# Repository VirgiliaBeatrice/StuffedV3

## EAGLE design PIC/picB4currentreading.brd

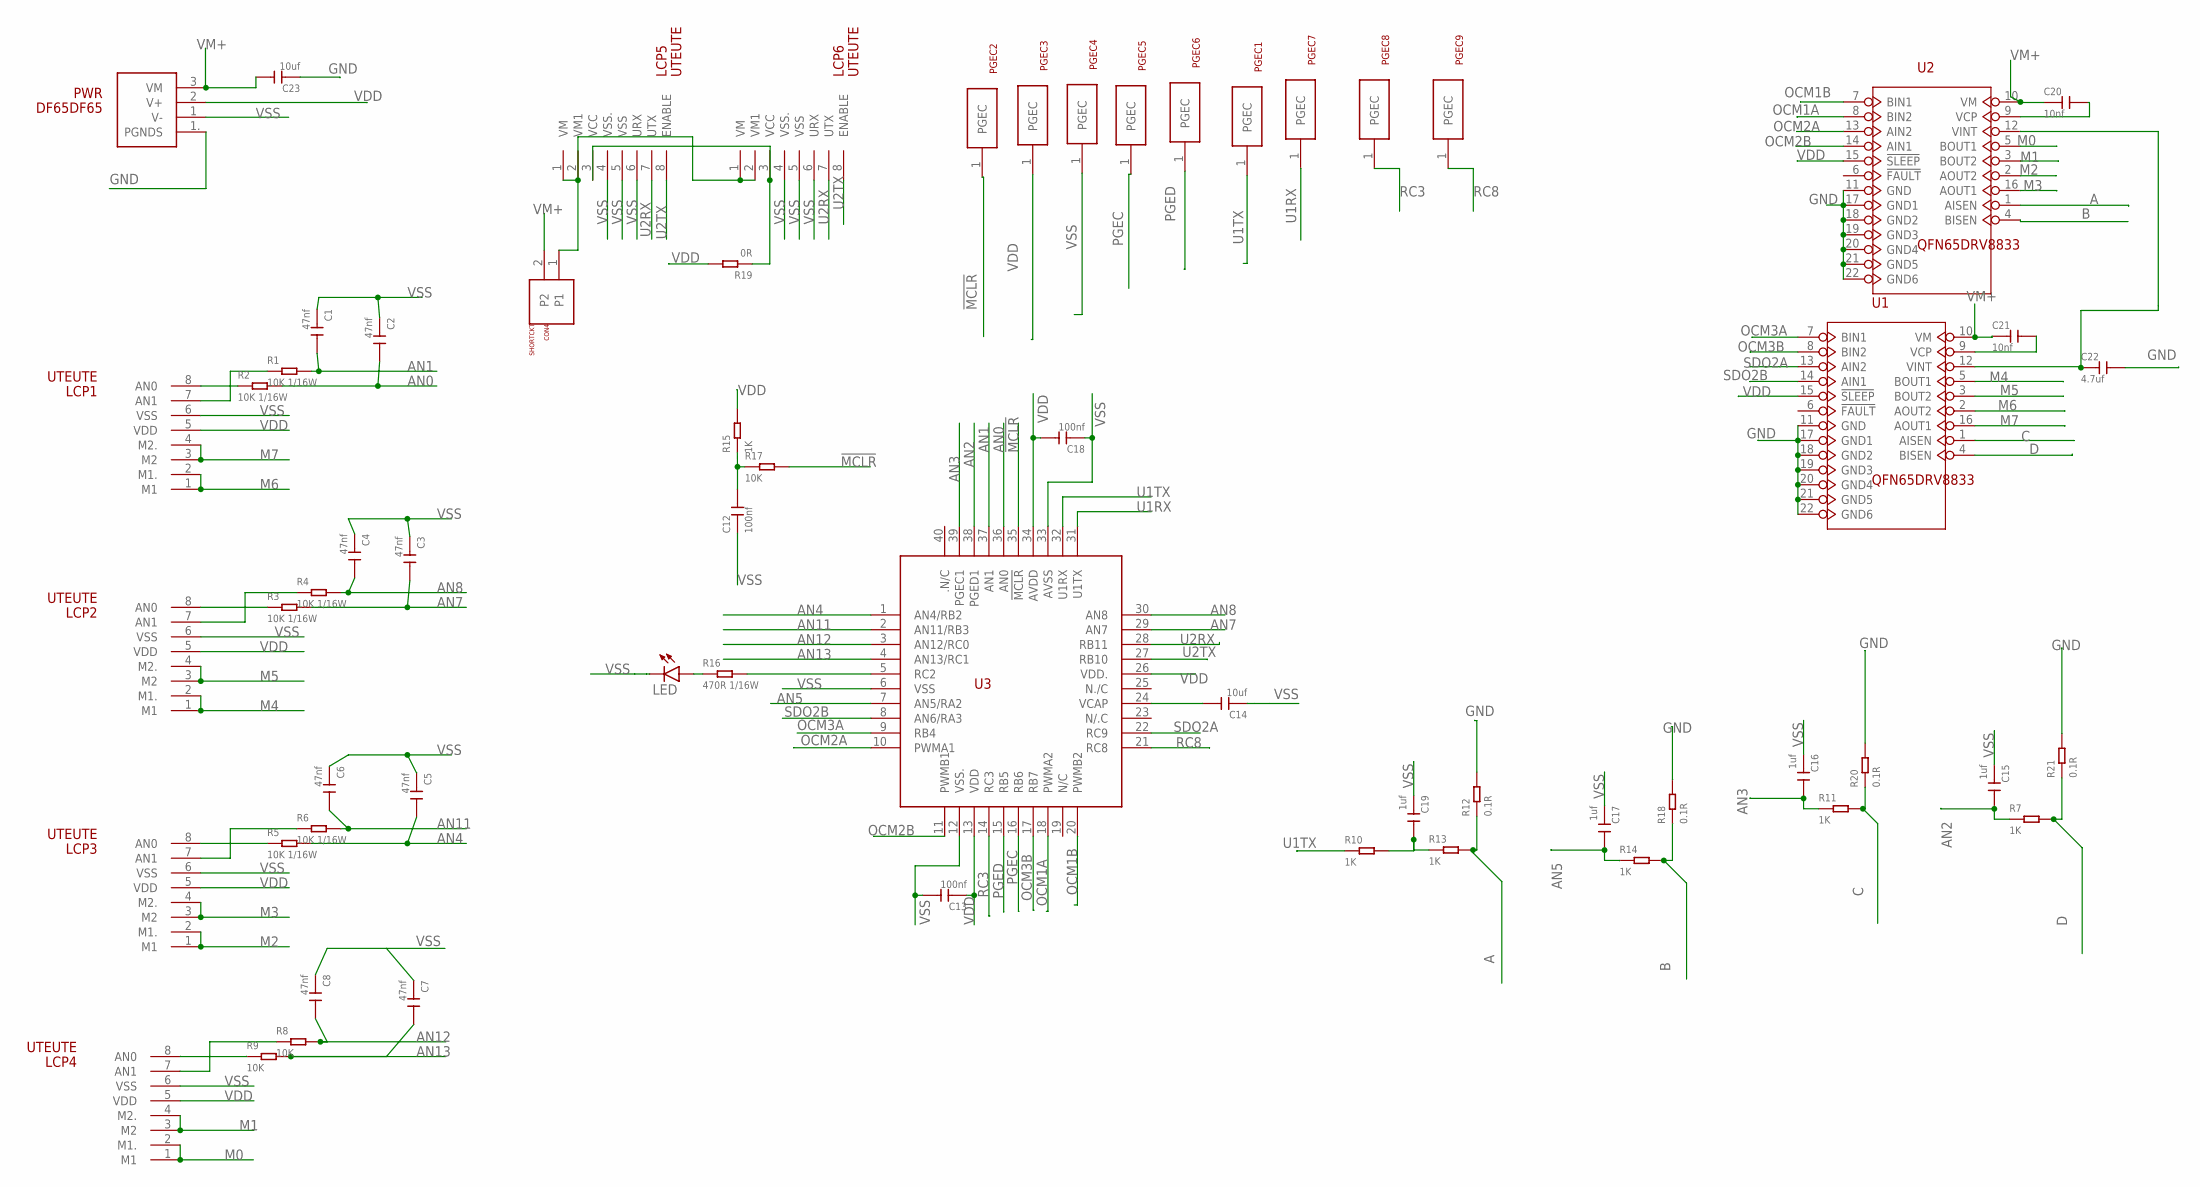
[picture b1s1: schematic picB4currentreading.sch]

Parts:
C1, C2, C3, C4, C5, C6, C7, C8: 47nf; C0402
C12, C13, C18: 100nf; C0402
C14, C23: 10uf; C0402
C15, C16, C17, C19: 1uf; C0402
C20, C21: 10nf; C0402
C22: 4.7uf; C0402
CON4: SHORTCKT; SHORT
LCP1, LCP2, LCP3, LCP4, LCP5, LCP6: UTEUTE; UTE
LED: LEDCHIP-LED0603; CHIP-LED0603
PGEC1, PGEC2, PGEC3, PGEC4, PGEC5, PGEC6, PGEC7, PGEC8, PGEC9: PGECPGEC; PGEC
PWR: DF65DF65; DF65
R1, R2, R3, R4, R5, R6: 10K 1/16W; R0402
R7, R10, R11, R13, R14, R15: 1K; R0402
R8, R9, R17: 10K; R0402
R12, R18, R20, R21: 0.1R; R0805
R16: 470R 1/16W; R0402
R19: 0R; R0402
U1, U2: QFN65DRV8833; QFN65P400X400X80-17N
U3: PIC32MM0064GPL036PIC32MM0064GPL36; UQFN40MV5X5MM

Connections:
!MCLR!: PGEC2.1, R17.2, U3.35 (!MCLR!)
A: R12.1, R13.2, U2.1 (AISEN)
AN0: C2.2, R2.2, U3.36 (AN0)
AN1: C1.2, R1.2, U3.37 (AN1)
AN2: C15.2, R7.1, U3.38 (PGED1)
AN3: C16.2, R11.1, U3.39 (PGEC1)
AN4: C5.2, R5.2, U3.1 (AN4/RB2)
AN5: C17.2, R14.1, U3.7 (AN5/RA2)
AN7: C3.2, R3.2, U3.29 (AN7)
AN8: C4.2, R4.2, U3.30 (AN8)
AN11: C6.2, R6.2, U3.2 (AN11/RB3)
AN12: C8.2, R8.2, U3.3 (AN12/RC0)
AN13: C7.2, R9.2, U3.4 (AN13/RC1)
B: R14.2, R18.1, U2.4 (BISEN)
C: R11.2, R20.1, U1.1 (AISEN)
D: R7.2, R21.1, U1.4 (BISEN)
GND: C22.2, C23.1, PWR.1. (PGNDS), R12.2, R18.2, R20.2, R21.2, U1.11 (GND), U1.17 (GND1), U1.18 (GND2), U1.19 (GND3), U1.20 (GND4), U1.21 (GND5), U1.22 (GND6), U2.11 (GND), U2.17 (GND1), U2.18 (GND2), U2.19 (GND3), U2.20 (GND4), U2.21 (GND5), U2.22 (GND6)
M0: LCP4.1 (M1), LCP4.2 (M1.), U2.5 (BOUT1)
M1: LCP4.3 (M2), LCP4.4 (M2.), U2.3 (BOUT2)
M2: LCP3.1 (M1), LCP3.2 (M1.), U2.2 (AOUT2)
M3: LCP3.3 (M2), LCP3.4 (M2.), U2.16 (AOUT1)
M4: LCP2.1 (M1), LCP2.2 (M1.), U1.5 (BOUT1)
M5: LCP2.3 (M2), LCP2.4 (M2.), U1.3 (BOUT2)
M6: LCP1.1 (M1), LCP1.2 (M1.), U1.2 (AOUT2)
M7: LCP1.3 (M2), LCP1.4 (M2.), U1.16 (AOUT1)
unnamed: LCP1.8 (AN0), R2.1
unnamed: C19.2, R10.2, R13.1
unnamed: LCP3.7 (AN1), R6.1
unnamed: CON4.1, LCP5.1 (VM), LCP5.2 (VM1), LCP6.1 (VM), LCP6.2 (VM1)
unnamed: LCP2.8 (AN0), R3.1
unnamed: LCP4.7 (AN1), R8.1
unnamed: LCP3.8 (AN0), R5.1
unnamed: LCP2.7 (AN1), R4.1
unnamed: LCP1.7 (AN1), R1.1
unnamed: C12.2, R15.1, R17.1
unnamed: R16.2, U3.5 (RC2)
unnamed: LED.A, R16.1
unnamed: LCP5.3 (VCC), LCP6.3 (VCC), R19.1
unnamed: LCP4.8 (AN0), R9.1
unnamed: C20.2, U2.9 (VCP)
unnamed: C21.2, U1.9 (VCP)
unnamed: C22.1, U1.12 (VINT), U2.12 (VINT)
unnamed: C14.2, U3.24 (VCAP)
OCM1A: U2.8 (BIN2), U3.18 (PWMA2)
OCM1B: U2.7 (BIN1), U3.20 (PWMB2)
OCM2A: U2.13 (AIN2), U3.10 (PWMA1)
OCM2B: U2.14 (AIN1), U3.11 (PWMB1)
OCM3A: U1.7 (BIN1), U3.9 (RB4)
OCM3B: U1.8 (BIN2), U3.17 (RB7)
PGEC: PGEC5.1, U3.16 (RB6)
PGED: PGEC6.1, U3.15 (RB5)
RC3: PGEC8.1, U3.14 (RC3)
RC8: PGEC9.1, U3.21 (RC8)
SDO2A: U1.13 (AIN2), U3.22 (RC9)
SDO2B: U1.14 (AIN1), U3.8 (AN6/RA3)
U1RX: PGEC7.1, U3.31 (U1TX)
U1TX: PGEC1.1, R10.1, U3.32 (U1RX)
U2RX: LCP5.7 (UTX), LCP6.7 (UTX), U3.28 (RB11)
U2TX: LCP5.8 (ENABLE), LCP6.8 (ENABLE), U3.27 (RB10)
VDD: C13.1, C18.2, LCP1.5 (VDD), LCP2.5 (VDD), LCP3.5 (VDD), LCP4.5 (VDD), PGEC3.1, PWR.2 (V+), R15.2, R19.2, U1.15 (!SLEEP!), U2.15 (!SLEEP!), U3.13 (VDD), U3.26 (VDD.), U3.34 (AVDD)
VM+: C20.1, C21.1, C23.2, CON4.2, PWR.3 (VM), U1.10 (VM), U2.10 (VM)
VSS: C1.1, C2.1, C3.1, C4.1, C5.1, C6.1, C7.1, C8.1, C12.1, C13.2, C14.1, C15.1, C16.1, C17.1, C18.1, C19.1, LCP1.6 (VSS), LCP2.6 (VSS), LCP3.6 (VSS), LCP4.6 (VSS), LCP5.4 (VSS.), LCP5.5 (VSS), LCP5.6 (URX), LCP6.4 (VSS.), LCP6.5 (VSS), LCP6.6 (URX), LED.C, PGEC4.1, PWR.1 (V-), U3.6 (VSS), U3.12 (VSS.), U3.33 (AVSS)

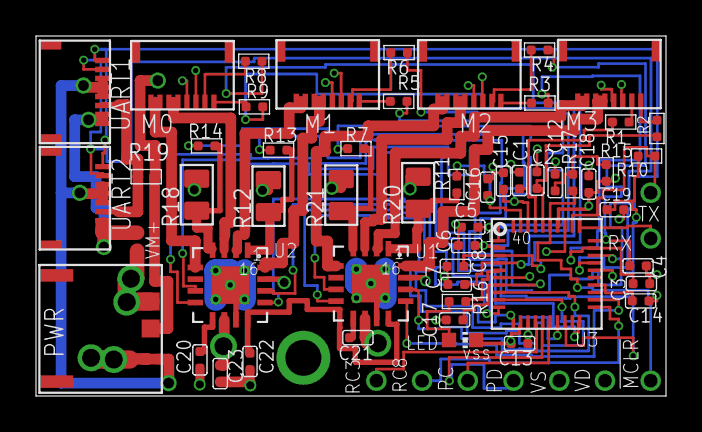
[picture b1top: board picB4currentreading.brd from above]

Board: 4 copper layers, 35.0 x 20.0 mm, 62 parts (0 on the bottom side), 62 nets.

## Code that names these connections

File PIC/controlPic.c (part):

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		if (ratio < 0){
			ratio = -ratio;
			CCP1CON2bits.OCAEN = 0;
			CCP1CON2bits.OCBEN = 1; //  OCM1B
		}else{
			CCP1CON2bits.OCAEN = 1; //  OCM1A
			CCP1CON2bits.OCBEN = 0;
		}
		CCP1RA = 0;
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	}else if (ch == 1){	//  M1=LCP3  U2A2/1=OCM2A/B
		if (ratio < 0){
			ratio = -ratio;
			RPOR1bits.RP6R = 6;		//	OCM2A
			RPOR4bits.RP20R = 0;	//	NC(PIO))
		}else{
			RPOR1bits.RP6R = 0;		//	NC(PIO))
			RPOR4bits.RP20R = 6;	//	OCM2B
		}
		CCP2RA = 0;
		CCP2RB = (unsigned)CCP2PR * ratio >> SDEC_BITS;
	}else if (ch == 2){
		if (ratio < 0){ //  M2=LCP2  U1B1/2=OCM3A/B
			ratio = -ratio;
			RPOR1bits.RP5R = 7;		//	=RB4: OCM3A
			RPOR2bits.RP11R = 0;	//	NC(PIO))
		}else{
			RPOR1bits.RP5R = 0;		//	NC(PIO))
			RPOR2bits.RP11R = 7;	//	=RB7: OCM3B
		}
		CCP3RA = 0;
		CCP3RB = (unsigned)CCP3PR * ratio >> SDEC_BITS;
    }else{	
		if (ratio < 0){ //  M3=LCP1 
			ratio = -ratio;
			RPOR4bits.RP19R = 3;	//=RC9:	SDO2
			RPOR0bits.RP4R = 0;		//	NC(PIO))
		}else{
			RPOR4bits.RP19R = 0;	//	NC(PIO))
			RPOR0bits.RP4R = 3;		//=RA3:	SDO2
		}
#ifdef SPIPWM128
		setSpiPwm128(ratio);
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
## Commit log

2019-10-24 Add some test code of SkiaSharp
2019-10-28 DrawPoint
2019-10-29 Add axes
2019-10-30 Add arrow line
2019-10-31 DrawArrow now is working well.
2019-10-31 1. Get clientSize correctly now. 2. Set local transform correctly now.
2019-11-01 [WIP] DrawAxes
2019-11-04 Correct transformation matrix for global and local coordinate transformation.
2019-11-04 Now system has correct ticks.
2019-11-05 Add hover feature.
2019-11-05 [WIP] Transformation
2019-11-05 Now system has correct Tranform Matrix.
2019-11-05 Correct display information of hover.
2019-11-05 Add a new indicator.
2019-11-06 Coordinates system has a correct scale matrix.
2019-11-06 1. Add a simple drag feature. 2. Double click to add a new point.
2019-11-12 Add a triangulation class for test.
2019-11-12 Correct transformation matrix, according to Entries
2019-11-12 Entries print out.
2019-11-12 Could do triangulation
2019-11-18 Visualize triangles.
2019-11-18 [WIP] chart extent.
2019-11-18 Padding
2019-11-19 Generalize whole transformation methods
2019-11-19 Add a new canvas for configuration space/
2019-11-19 Add some button controls, and resize the form.
2019-11-19 Create a initialization method.
2019-11-19 Correct initial triangle rendering.
2019-11-19 Add a simple mapping class.
2019-11-19 Click right button to add testpoint.
2019-11-19 Right button dragging function.
2019-11-19 [WIP] interpolation
2019-11-19 Correct interpolation miss.
2019-11-19 Triangle hover feature, but precision bug exists
2019-11-27 Correct determination of a point inside a triangle. Need more improve.
2019-11-28 1. Oriented Triangle 2. Save to png
2019-12-16 fix: correct dragging feature of ConfigurationCanvas
2019-12-16 perf: remove some debug info
    Confirm the debugging info of "thread exit".
2019-12-18 feat: re-drawing while dragging
    [WIP]
2019-12-19 feat: re-drawing while dragging
2019-12-23 refactor: rename class name from plural style to collection style
    - `Entries` to `EntryCollection`
    - `Triangle` to `TriangleCollection`
2019-12-23 refactor: rename class name from plural style to collection style
    - `TriVertices` to `TriVertexCollection`
    - Clear some comments
2019-12-24 refactor!: re-design `isInZone` method
    BREAKING CHANGE: refactor `isInZone` method and `MouseMove` events
2019-12-26 refactor!: refactor some methods
    BREAKING CHANGE:
    - chart.IsInZone
    - chart.IsInTriangle
    - chart.IsInArea
    - Add update methods into EntryCollection and TriangleCollection
    - Delete unnecessary methods in chart
2020-01-09 refactor: re-construct ConfigurationCanvas's IsInControlArea method
2020-01-09 feat: add keyboard shortcut feature
    - Key e for EdittingState
    - key escape for quitting all editting mode
2020-01-10 feat: make only single entry could be selected
2020-01-10 feat: add re-scale feature
    - push F to re-scale
2020-01-13 fix: pop message when no entry is being selected
2020-01-14 feat!: correctly interpolate in different simplices
    - Currently, extrapolation feature has been removed.
    - Extrapolation feature will be added in future update.
    BREAKING CHANGE: refactor SimplicialComplex part
2020-01-14 fix: do not interpolate when simplices have not prepared
2020-01-15 fix: add lost packages.config file
2020-01-15 fix: add missing project configuration files
2020-01-16 feat: calculate convex hull based on all entries
2020-01-16 feat: add DrawRay method
2020-01-16 feat: add centroids for extreme points of convex hull
2020-01-16 feat: add color transition
2020-01-17 feat: add new method for splitting zones
2020-01-17 fix: simplex interpolation now is working well while adjusting paired Entry
2020-07-17 refactor!: Refactor reparameterization processing
2020-07-17 feat: Add PCController as reference
    - Add delegate to communicate with two form.
2020-07-17 feat: connect with PCController
2020-07-19 feat: PCContoller now could be invoked manually
2020-07-19 refactor: ConfigurationSpace should be inherited
    - Clean some unnecessary code.
2020-07-20 feat: precise hover feature
2020-08-11 feat: add several new features
    - Add libqhull_csharp.dll support.
    - Add extension line displaying.
2020-08-11 feat: color gradient
2020-08-13 feat: new transformation matrix
2020-08-30 feat: new canvas architecture(dev)
2020-08-30 feat: scale feature
2020-08-31 feat: drag and drop behavior
2020-09-01 feat: add selectable component
2020-09-01 feat: drag and drop feature on grid
2020-09-14 feat: pan and zoom for scene
2020-09-14 fix: drag and drop bugs
    - Right button to drag on canvas
2020-09-14 fix: OnSizeChanged bug
2020-09-14 feat: click to select
    - Click to select.
    - Only selected obejct could be dragged.
2020-09-15 feat: add new hover event
2020-09-16 feat: add treeview for editor feature
2020-09-18 perf: performance optimization when onPaint
2020-09-21 feat: clipping ray in viewport
2020-09-25 feat: add extension ray to target ridges
2020-10-06 feat: add exterior zone for triangles
2020-10-19 [WIP] - dual windows
2020-10-19 feat: vertex normal splitting method
2020-11-04 feat: voronoi region paint
2020-11-05 feat: voronoi region now is clipping correctly
2020-11-05 feat: event dispatcher now binds with scene
2020-11-22 feat: configuation space now is drawable
2020-11-22 feat: treenode has invisible feature
2020-11-22 refactor: follow new CanvasObject interface
2020-11-23 feat: [Experimental]new behavior system
2020-11-23 feat: state manager
2020-11-24 feat: new system of behavior
2020-11-24 feat: simplex pairing
2020-11-25 feat: running instance
2020-11-25 feat: extrapolation
2020-12-01 fix: force control refresh to redraw
2020-12-21 feat: new mouse event handler
2020-12-21 feat: add back zoom feature
2021-09-01 fix: some bugs
2021-09-01 feat: version up
2021-09-02 feat: new form
2021-09-03 feat: selection and triangulation
2021-09-03 feat: motor configuration
2021-09-03 feat: LinearSlider
2021-09-03 misc: add gitignore
2021-09-04 feat: pointer
2021-09-05 feat: move to new solution
    - Solved the usercontrol exception
    - Move to new folder to keep projec clean
2021-09-05 feat: layer feature
2021-09-05 feat: add trace
2021-09-05 feat: manipulation
2021-09-05 feat: add config class
2021-09-06 feat: first running example
2021-09-06 feat: new property form
2021-09-07 feat: layer
2021-09-07 feat: node editting
2021-09-07 feat: adjust edit
2021-09-07 feat: delete nodes
2021-09-07 feat: shortcuts
2021-09-07 feat: working normal after editing
2021-09-07 feat: update canvas when lost focus of subform
2021-09-07 feat: working sample
2021-09-07 feat: layer property could be called from right click
2021-09-07 feat: dnd of layers
2021-09-07 feat: unpair feature
2021-09-07 feat: setting close behavior
2021-09-07 feat: new motorcontoller
2021-09-07 feat: motor controller handle offset
2021-09-07 dev: WIP
2021-09-08 bugfix
2021-09-08 feat: motor control
2021-09-08 feat: fix Config bary. not update
2021-09-08 feat: delete confirm
2021-09-09 feat: fix bugs
2021-09-09 feat: all return zero
2021-09-09 feat: all return zero autosize
2021-09-13 feat: ray intersection
2021-09-20 feat: split voronoi region
2021-09-20 dev: clip
2021-09-30 feat: drawing exterior
2021-09-30 fix: ccw/cw
2021-10-02 dev: test pass
2021-10-02 feat: exterior region drawing
2021-10-02 tag: exterior
2021-10-02 fix: unsolved merging
2021-10-02 feat: exterior of one simplex
2021-10-03 feat: new simplicial mapping implementation
2021-10-03 feat: change to gl
2021-10-03 fix: case single simplex
2021-10-03 feat: mini canvas could pan
2021-10-03 dev: undo
2021-10-04 feat: new layer structure
2021-10-04 fix: D&D of treeview
2021-10-04 fix: correct behavior of Layer
2021-10-04 dev: save feature
2021-10-04 feat: save&load
2021-10-05 feat: save and load by selecting folder
2021-10-05 feat: save improvement
2021-10-05 feat: working for robot
2021-10-05 fix: SelectableLayer correctly be generated
2021-10-05 fix: correct layer behavior in target selection
2021-10-05 fix: correct behavior of adding new node on old configuration
2021-10-05 feat: pan feature on main canvas
2021-10-05 fix: chain
2021-10-05 feat: new paint of selection tool
2021-10-05 feat: trace appearance
2021-10-05 misc
2021-10-06 feat: multiple complexes in one layer
    - fix: one simplex ccw order
2021-10-08 feat: pair all feature
2021-10-08 fix: ndarray construction bugs
2021-10-08 feat: correct interpolating behavior
2021-10-08 fix: interpolating bug in circular sector
2021-10-08 fix: calculating curve dividing by 0
2021-10-08 back: back to selected layer display mode
2021-10-08 feat: tensor style
2021-10-08 fix: tiny canvas bugs
2021-10-09 feat: multibary support
2021-10-09 misc: clean unnecessary comments
2021-10-10 dev: node editor
2021-10-12 misc: add ignore
2021-10-12 dev:
2021-10-26 feat: correct draw behavior
2021-10-26 fix: color
2021-10-28 step: left to motor
2021-10-28 step: right to motor
2021-10-28 step: multilinear working
2021-10-28 feat: 1-simplex
2021-10-28 feat: controller back to centroid
2021-10-29 feat
2021-10-29 feat: index label
2021-10-30 feat: matrix version of pairing.
2021-10-30 fix: mapto
2021-10-30 feat: async interpolation
2021-10-30 still have bug in 2d tensor
2021-10-30 feat: save
2021-10-31 fix: tag
2021-10-31 feat: motor value send in 10ms period and in queue
2021-10-31 feat: matrix clcik animation
2021-10-31 feat: F12 for debug info
2021-11-01 fix: out of range and panel controller
2022-03-10 WIP with ctx recursively function
